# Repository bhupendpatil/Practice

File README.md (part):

<!-- prettier-ignore-start -->
# Practice

## Python
Program | Link
-- | --
Addition of Matrix | [.py](https://github.com/bhupendpatil/Practice/blob/master/Python/Addition%20of%20Matrix.py)
Bubble Sorting | [.py](https://github.com/bhupendpatil/Practice/blob/master/Python/Bubble%20Sorting.py)
Efficient Sorting | [.py](https://github.com/bhupendpatil/Practice/blob/master/Python/Efficient%20Sorting.py)
Infix to PostFix | [.py](https://github.com/bhupendpatil/Practice/blob/master/Python/Infix%20to%20PostFix.py)
Insertion Sorting | [.py](https://github.com/bhupendpatil/Practice/blob/master/Python/Insertion%20Sorting.py)
Linked List | [.py](https://github.com/bhupendpatil/Practice/blob/master/Python/Linked%20List.py)
Matching Deli | [.py](https://github.com/bhupendpatil/Practice/blob/master/Python/Matching%20Deli.py)
Palindrom Number | [.py](https://github.com/bhupendpatil/Practice/blob/master/Python/Palindrom%20Number.py)
Para Check_html | [.py](https://github.com/bhupendpatil/Practice/blob/master/Python/Para%20Check_html.py)
Para Checker | [.py](https://github.com/bhupendpatil/Practice/blob/master/Python/Para%20Checker.py)
Program based loop for odd and even numbers | [.py](https://github.com/bhupendpatil/Practice/blob/master/Python/Program%20based%20loop%20for%20odd%20and%20even%20numbers.py)
Program based on Reverse of 2 numbers | [.py](https://github.com/bhupendpatil/Practice/blob/master/Python/Program%20based%20on%20Reverse%20of%202%20numbers.py)
Program based on Reverse of 3 digit numbers | [.py](https://github.com/bhupendpatil/Practice/blob/master/Python/Program%20based%20on%20Reverse%20of%203%20digit%20numbers.py)
Program based on Reverse of 4 digit numbers using math | [.py](https://github.com/bhupendpatil/Practice/blob/master/Python/Program%20based%20on%20Reverse%20of%204%20digit%20numbers%20using%20math.py)
Program based on Swapping of two numbers | [.py](https://github.com/bhupendpatil/Practice/blob/master/Python/Program%20based%20on%20Swapping%20of%20two%20numbers.py)
Program based on loop for prime numbers | [.py](https://github.com/bhupendpatil/Practice/blob/master/Python/Program%20based%20on%20loop%20for%20prime%20numbers.py)
Program based on loops for table | [.py](https://github.com/bhupendpatil/Practice/blob/master/Python/Program%20based%20on%20loops%20for%20table.py)
Program based on to check whether the day is hot or cold | [.py](https://github.com/bhupendpatil/Practice/blob/master/Python/Program%20based%20on%20to%20check%20whether%20the%20day%20is%20hot%20or%20cold.py)
Program to check even and odd | [.py](https://github.com/bhupendpatil/Practice/blob/master/Python/Program%20to%20check%20even%20and%20odd.py)
Program to check positive or negative if it is positive then check weather it is even or odd | [.py](https://github.com/bhupendpatil/Practice/blob/master/Python/Program%20to%20check%20positive%20or%20negative%20if%20it%20is%20positive%20then%20check%20weather%20it%20is%20even%20or%20odd.py)
Program to check positive or negative or zero | [.py](https://github.com/bhupendpatil/Practice/blob/master/Python/Program%20to%20check%20positive%20or%20negative%20or%20zero.py)
Program to check whether a person is in profit or loss | [.py](https://github.com/bhupendpatil/Practice/blob/master/Python/Program%20to%20check%20whether%20a%20person%20is%20in%20profit%20or%20loss.py)
Properties | [.py](https://github.com/bhupendpatil/Practice/blob/master/Python/Properties.py)
Search Result | [.py](https://github.com/bhupendpatil/Practice/blob/master/Python/Search%20Result.py)
Simulation of Hot Potato game | [.py](https://github.com/bhupendpatil/Practice/blob/master/Python/Simulation%20of%20Hot%20Potato%20game.py)
Square Matrix | [.py](https://github.com/bhupendpatil/Practice/blob/master/Python/Square%20Matrix.py)
Stack | [.py](https://github.com/bhupendpatil/Practice/blob/master/Python/Stack.py)
String Reverse | [.py](https://github.com/bhupendpatil/Practice/blob/master/Python/String%20Reverse.py)
Absolute Sorting | [.py](https://github.com/bhupendpatil/Practice/blob/master/Python/CheckiO/Elementary/Absolute%20Sorting.py)
Binary Count | [.py](https://github.com/bhupendpatil/Practice/blob/master/Python/CheckiO/Elementary/Binary%20Count.py)
Boolean Algebra | [.py](https://github.com/bhupendpatil/Practice/blob/master/Python/CheckiO/Elementary/Boolean%20Algebra.py)
Building Base | [.py](https://github.com/bhupendpatil/Practice/blob/master/Python/CheckiO/Elementary/Building%20Base.py)
Common Words | [.py](https://github.com/bhupendpatil/Practice/blob/master/Python/CheckiO/Elementary/Common%20Words.py)
Count Inversion | [.py](https://github.com/bhupendpatil/Practice/blob/master/Python/CheckiO/Elementary/Count%20Inversion.py)
Days Between | [.py](https://github.com/bhupendpatil/Practice/blob/master/Python/CheckiO/Elementary/Days%20Between.py)
Digits Multiplication | [.py](https://github.com/bhupendpatil/Practice/blob/master/Python/CheckiO/Elementary/Digits%20Multiplication.py)
Even the last | [.py](https://github.com/bhupendpatil/Practice/blob/master/Python/CheckiO/Elementary/Even%20the%20last.py)
Fizz Buzz | [.py](https://github.com/bhupendpatil/Practice/blob/master/Python/CheckiO/Elementary/Fizz%20Buzz.py)
Friends | [.py](https://github.com/bhupendpatil/Practice/blob/master/Python/CheckiO/Elementary/Friends.py)
Index Power | [.py](https://github.com/bhupendpatil/Practice/blob/master/Python/CheckiO/Elementary/Index%20Power.py)
Monkey Typing | [.py](https://github.com/bhupendpatil/Practice/blob/master/Python/CheckiO/Elementary/Monkey%20Typing.py)
Most Numbers | [.py](https://github.com/bhupendpatil/Practice/blob/master/Python/CheckiO/Elementary/Most%20Numbers.py)
Number Base | [.py](https://github.com/bhupendpatil/Practice/blob/master/Python/CheckiO/Elementary/Number%20Base.py)
Pangram | [.py](https://github.com/bhupendpatil/Practice/blob/master/Python/CheckiO/Elementary/Pangram.py)
Right to Left | [.py](https://github.com/bhupendpatil/Practice/blob/master/Python/CheckiO/Elementary/Right%20to%20Left.py)
Secret Message | [.py](https://github.com/bhupendpatil/Practice/blob/master/Python/CheckiO/Elementary/Secret%20Message.py)
The end of other | [.py](https://github.com/bhupendpatil/Practice/blob/master/Python/CheckiO/Elementary/The%20end%20of%20other.py)
Three Words | [.py](https://github.com/bhupendpatil/Practice/blob/master/Python/CheckiO/Elementary/Three%20Words.py)
Feed Pigeons | [.py](https://github.com/bhupendpatil/Practice/blob/master/Python/CheckiO/Home/Feed%20Pigeons.py)
House Password | [.py](https://github.com/bhupendpatil/Practice/blob/master/Python/CheckiO/Home/House%20Password.py)
How to find friends | [.py](https://github.com/bhupendpatil/Practice/blob/master/Python/CheckiO/Home/How%20to%20find%20friends.py)
Median | [.py](https://github.com/bhupendpatil/Practice/blob/master/Python/CheckiO/Home/Median.py)
Moore Neighbourhood | [.py](https://github.com/bhupendpatil/Practice/blob/master/Python/CheckiO/Home/Moore%20Neighbourhood.py)
Non-unique Elements | [.py](https://github.com/bhupendpatil/Practice/blob/master/Python/CheckiO/Home/Non-unique%20Elements.py)
Pawn Brotherhood | [.py](https://github.com/bhupendpatil/Practice/blob/master/Python/CheckiO/Home/Pawn%20Brotherhood.py)
The Flat Dictionary | [.py](https://github.com/bhupendpatil/Practice/blob/master/Python/CheckiO/Home/The%20Flat%20Dictionary.py)
The Longest Palindromic | [.py](https://github.com/bhupendpatil/Practice/blob/master/Python/CheckiO/Home/The%20Longest%20Palindromic.py)
The Most Wanted Letter | [.py](https://github.com/bhupendpatil/Practice/blob/master/Python/CheckiO/Home/The%20Most%20Wanted%20Letter.py)
Xs and Os Referee | [.py](https://github.com/bhupendpatil/Practice/blob/master/Python/CheckiO/Home/Xs%20and%20Os%20Referee.py)
GCD | [.py](https://github.com/bhupendpatil/Practice/blob/master/Python/GCD.py) [.py](https://github.com/bhupendpatil/Practice/blob/master/Python/GCDLessTime.py) [.py](https://github.com/bhupendpatil/Practice/blob/master/Python/GCDmoreLessTime.py)
Insertion sort | [.py](https://github.com/bhupendpatil/Practice/blob/master/Python/1insertionSort.py) [.py](https://github.com/bhupendpatil/Practice/blob/master/Python/insertion.py)
Merge sort | [.py](https://github.com/bhupendpatil/Practice/blob/master/Python/2mergeSort.py) [.py](https://github.com/bhupendpatil/Practice/blob/master/Python/merge.py)
Permute by sorting | [.py](https://github.com/bhupendpatil/Practice/blob/master/Python/3ipermuteBySort.py)
Permute by cyclic | [.py](https://github.com/bhupendpatil/Practice/blob/master/Python/3iipermuteByCyclic.py)
Longest Common Subsequence | [.py](https://github.com/bhupendpatil/Practice/blob/master/Python/4longestCS.py) [.py](https://github.com/bhupendpatil/Practice/blob/master/Python/LCS.py)
Huffman's code | [.py](https://github.com/bhupendpatil/Practice/blob/master/Python/5huffman.py)
Kruskal's code | [.py](https://github.com/bhupendpatil/Practice/blob/master/Python/6kruskal.py)
Dijkstra's code | [.py](https://github.com/bhupendpatil/Practice/blob/master/Python/7dijkstra.py)
Euclid's code | [.py](https://github.com/bhupendpatil/Practice/blob/master/Python/8euclid.py) [ckt.py](https://github.com/bhupendpatil/Practice/blob/master/Python/euclid.py)
Euler's Theorem | [.py](https://github.com/bhupendpatil/Practice/blob/master/Python/9eulers.py)
Fermat's Theorem | [.py](https://github.com/bhupendpatil/Practice/blob/master/Python/9fermat.py)
Robot with Gear | [.py](https://github.com/bhupendpatil/Practice/blob/master/Python/Robotics/robotWithGear.py)
Robot without Gear | [.py](https://github.com/bhupendpatil/Practice/blob/master/Python/Robotics/robotWithoutGear.py)
Forward, Left, Right | [.py](https://github.com/bhupendpatil/Practice/blob/master/Python/Robotics/forwardLeftAndRight.py)
Light sensors to follow a line | [.py](https://github.com/bhupendpatil/Practice/blob/master/Python/Robotics/LightSensor.py)
Path following Robot | [.py](https://github.com/bhupendpatil/Practice/blob/master/Python/Robotics/PathFollowing.py)
Register obstacles | [.py](https://github.com/bhupendpatil/Practice/blob/master/Python/Robotics/RegisterObstacles.py)
BFS | [.py](https://github.com/bhupendpatil/Practice/blob/master/Python/BFS.py)
Do a Square (while loop) | [.py](https://github.com/bhupendpatil/Practice/blob/master/Python/Robotics/doSquareWhile.py)
Doing Steps (for loop) | [.py](https://github.com/bhupendpatil/Practice/blob/master/Python/Robotics/stepsFor.py)
Change direction based on condition | [.py](https://github.com/bhupendpatil/Practice/blob/master/Python/Robotics/directionCondition.py)
Control speed using switch case | [.py](https://github.com/bhupendpatil/Practice/blob/master/Python/Robotics/controlSpeedSwitch.py)
Simple Class | [.py](https://github.com/bhupendpatil/Practice/blob/master/Python/oopsSimp.py)
OOP init | [.py](https://github.com/bhupendpatil/Practice/blob/master/Python/oopsInit.py) [.py](https://github.com/bhupendpatil/Practice/blob/master/Python/oopsInit2.py)
OOP inheritance | [.py](https://github.com/bhupendpatil/Practice/blob/master/Python/oopsInheritance.py)
OOP overriding and overloading | [.py](https://github.com/bhupendpatil/Practice/blob/master/Python/oopsOver.py)
OOP Encapsulation | [.py](https://github.com/bhupendpatil/Practice/blob/master/Python/oopsEncapsulation.py)
OOP Private | [.py](https://github.com/bhupendpatil/Practice/blob/master/Python/oopsPrivate.py)
OOP Polymorphism | [.py](https://github.com/bhupendpatil/Practice/blob/master/Python/oopsPolymorphism.py)
Numpy Array and List | [.py](https://github.com/bhupendpatil/Practice/blob/master/Python/numpyBoot.py)
Matplotlib Boot | [.py](https://github.com/bhupendpatil/Practice/blob/master/Python/matplotlibBoot.py)
Pandas Boot | [.py](https://github.com/bhupendpatil/Practice/blob/master/Python/pandasBoot.py) [.py](https://github.com/bhupendpatil/Practice/blob/master/ML/Pandas/introduction-to-pandas.py)
Seaborn Boot | [.py](https://github.com/bhupendpatil/Practice/blob/master/Python/seabornBoot.py)

## Java
Program | Link
-- | --
AreaOfCircle | [.java](https://github.com/bhupendpatil/Practice/blob/master/Java/AreaOfCircle.java)
AreaOfRectangle | [.java](https://github.com/bhupendpatil/Practice/blob/master/Java/AreaOfRectangle.java)
AverageElement | [.java](https://github.com/bhupendpatil/Practice/blob/master/Java/AverageElement.java)
CalculateSimpleInterest | [.java](https://github.com/bhupendpatil/Practice/blob/master/Java/CalculateSimpleInterest.java)
Calculator | [.java](https://github.com/bhupendpatil/Practice/blob/master/Java/Calculator.java)
CirclePerimeter | [.java](https://github.com/bhupendpatil/Practice/blob/master/Java/CirclePerimeter.java)
ConstructorOverloadingg | [.java](https://github.com/bhupendpatil/Practice/blob/master/Java/ConstructorOverloadingg.java)
Constructorr | [.java](https://github.com/bhupendpatil/Practice/blob/master/Java/Constructorr.java)
EvenNumberList | [.java](https://github.com/bhupendpatil/Practice/blob/master/Java/EvenNumberList.java)
EvenOddNumber | [.java](https://github.com/bhupendpatil/Practice/blob/master/Java/EvenOddNumber.java)
ExceptionHandelingg | [.java](https://github.com/bhupendpatil/Practice/blob/master/Java/ExceptionHandelingg.java)
Factorial | [.java](https://github.com/bhupendpatil/Practice/blob/master/Java/Factorial.java)
FibonacciSeries | [.java](https://github.com/bhupendpatil/Practice/blob/master/Java/FibonacciSeries.java)
HelloWorld | [.java](https://github.com/bhupendpatil/Practice/blob/master/Java/HelloWorld.java)
InhertTest | [.java](https://github.com/bhupendpatil/Practice/blob/master/Java/InhertTest.java)
InterfaceTest | [.java](https://github.com/bhupendpatil/Practice/blob/master/Java/InterfaceTest.java)
JavaClasss | [.java](https://github.com/bhupendpatil/Practice/blob/master/Java/JavaClasss.java)
JavaObject | [.java](https://github.com/bhupendpatil/Practice/blob/master/Java/JavaObject.java)
MethodsOverloadingg | [.java](https://github.com/bhupendpatil/Practice/blob/master/Java/MethodsOverloadingg.java)
MultiInheritance | [.java](https://github.com/bhupendpatil/Practice/blob/master/Java/MultiInheritance.java)
MultiThreadingg | [.java](https://github.com/bhupendpatil/Practice/blob/master/Java/MultiThreadingg.java)
MultipleCatchBlock | [.java](https://github.com/bhupendpatil/Practice/blob/master/Java/MultipleCatchBlock.java)
NestingOfMethodss | [.java](https://github.com/bhupendpatil/Practice/blob/master/Java/NestingOfMethodss.java)
OddNumberList | [.java](https://github.com/bhupendpatil/Practice/blob/master/Java/OddNumberList.java)
OverRidingg | [.java](https://github.com/bhupendpatil/Practice/blob/master/Java/OverRidingg.java)
RectanglePerimeter | [.java](https://github.com/bhupendpatil/Practice/blob/master/Java/RectanglePerimeter.java)
ReversalOfAnyNumber | [.java](https://github.com/bhupendpatil/Practice/blob/master/Java/ReversalOfAnyNumber.java)
Reversalof2digits | [.java](https://github.com/bhupendpatil/Practice/blob/master/Java/Reversalof2digits.java)
Reversalof3digits | [.java](https://github.com/bhupendpatil/Practice/blob/master/Java/Reversalof3digits.java)
RunnableTest | [.java](https://github.com/bhupendpatil/Practice/blob/master/Java/RunnableTest.java)
SaralPyramid | [.java](https://github.com/bhupendpatil/Practice/blob/master/Java/SaralPyramid.java)
SingleInheritance | [.java](https://github.com/bhupendpatil/Practice/blob/master/Java/SingleInheritance.java)
SwapTwoNumbers | [.java](https://github.com/bhupendpatil/Practice/blob/master/Java/SwapTwoNumbers.java)
ThreadMethods | [.java](https://github.com/bhupendpatil/Practice/blob/master/Java/ThreadMethods.java)
ThreadPriority | [.java](https://github.com/bhupendpatil/Practice/blob/master/Java/ThreadPriority.java)
ThreadTest | [.java](https://github.com/bhupendpatil/Practice/blob/master/Java/ThreadTest.java)
TotalArea | [.java](https://github.com/bhupendpatil/Practice/blob/master/Java/TotalArea.java)
TypeCasting | [.java](https://github.com/bhupendpatil/Practice/blob/master/Java/TypeCasting.java)
UltaPyramid | [.java](https://github.com/bhupendpatil/Practice/blob/master/Java/UltaPyramid.java)
halfPyramid | [.java](https://github.com/bhupendpatil/Practice/blob/master/Java/halfPyramid.java)
Calculator | [.java](https://github.com/bhupendpatil/Practice/blob/master/Java/Calculator.java) [.java](https://github.com/bhupendpatil/Practice/blob/master/Java/Calculator_Design.java)
JComboBox | [.java](https://github.com/bhupendpatil/Practice/blob/master/Java/ComboBox.java)
Action Event | [.java](https://github.com/bhupendpatil/Practice/blob/master/Java/DemoActionEvent.java)
JButton | [.java](https://github.com/bhupendpatil/Practice/blob/master/Java/DemoButton.java)
JDBC | [.java](https://github.com/bhupendpatil/Practice/blob/master/Java/DemoDatabaseJDBC.java) [.java](https://github.com/bhupendpatil/Practice/blob/master/Java/DemoJDBC.java)
JDBC output | [.java](https://github.com/bhupendpatil/Practice/blob/master/Java/DatabaseTableOutput.java)
JDialog | [.java](https://github.com/bhupendpatil/Practice/blob/master/Java/DemoDialog.java)
JColorChooser | [.java](https://github.com/bhupendpatil/Practice/blob/master/Java/DemoJColorChooser.java) [.java](https://github.com/bhupendpatil/Practice/blob/master/Java/ColorChooser5.java)
JDesktopPane | [.java](https://github.com/bhupendpatil/Practice/blob/master/Java/DemoJDesktopPane.java) [.java](https://github.com/bhupendpatil/Practice/blob/master/Java/DesktopPane4.java)
JFileChooser | [.java](https://github.com/bhupendpatil/Practice/blob/master/Java/DemoJFileChooser.java)
JScrollPane | [.java](https://github.com/bhupendpatil/Practice/blob/master/Java/DemoJScrollPane.java) [.java](https://github.com/bhupendpatil/Practice/blob/master/Java/ScrollPane2.java)
JTabbedPane | [.java](https://github.com/bhupendpatil/Practice/blob/master/Java/DemoJTabbedPane.java) [.java](https://github.com/bhupendpatil/Practice/blob/master/Java/TabbedPane.java) [.java](https://github.com/bhupendpatil/Practice/blob/master/Java/TabbedPane3.java)
JTable | [.java](https://github.com/bhupendpatil/Practice/blob/master/Java/DemoJTable.java) [.java](https://github.com/bhupendpatil/Practice/blob/master/Java/Tablee.java) [.java](https://github.com/bhupendpatil/Practice/blob/master/Java/Table6.java)
JTextArea | [.java](https://github.com/bhupendpatil/Practice/blob/master/Java/DemoJTextArea.java)
JTextField | [.java](https://github.com/bhupendpatil/Practice/blob/master/Java/DemoJTextField.java)
JTree | [.java](https://github.com/bhupendpatil/Practice/blob/master/Java/DemoJTree.java) [.java](https://github.com/bhupendpatil/Practice/blob/master/Java/Tree7.java)
Key Event | [.java](https://github.com/bhupendpatil/Practice/blob/master/Java/DemoKeyEvent.java)
JMenu | [.java](https://github.com/bhupendpatil/Practice/blob/master/Java/DemoMenu.java)
JDBC MetaData | [.java](https://github.com/bhupendpatil/Practice/blob/master/Java/DemoMetaData.java)
Mouse Event | [.java](https://github.com/bhupendpatil/Practice/blob/master/Java/DemoMouseEvent.java)
JOptionPane | [.java](https://github.com/bhupendpatil/Practice/blob/master/Java/DemoOptionPane.java)
MultiThreading Runnable | [.java](https://github.com/bhupendpatil/Practice/blob/master/Java/DemoRunnable.java)	 
Signin Form | [.java](https://github.com/bhupendpatil/Practice/blob/master/Java/DemoSignin.java) [.java](https://github.com/bhupendpatil/Practice/blob/master/Java/LoginForm.java) [.java](https://github.com/bhupendpatil/Practice/blob/master/Java/TextAndPasswordFieldJ.java) [.java](https://github.com/bhupendpatil/Practice/blob/master/Java/Login1.java)
JSplitPane | [.java](https://github.com/bhupendpatil/Practice/blob/master/Java/DemoSplitPane.java) [.java](https://github.com/bhupendpatil/Practice/blob/master/Java/SplitPane.java)
MultiThreading Thread | [.java](https://github.com/bhupendpatil/Practice/blob/master/Java/DemoThread.java)
Window Event | [.java](https://github.com/bhupendpatil/Practice/blob/master/Java/DemoWindowEvent.java)	 
IPAddress | [.java](https://github.com/bhupendpatil/Practice/blob/master/Java/IPAddress.java)	 
IPAddress Using LH | [.java](https://github.com/bhupendpatil/Practice/blob/master/Java/IPAddressUsingLH.java)	 
InternalFrame | [.java](https://github.com/bhupendpatil/Practice/blob/master/Java/InternalFrame.java)	 
JLabel | [.java](https://github.com/bhupendpatil/Practice/blob/master/Java/LabelJ.java)
Loading | [.java](https://github.com/bhupendpatil/Practice/blob/master/Java/Loading.java)	 	 
Mixture | [.java](https://github.com/bhupendpatil/Practice/blob/master/Java/Mixture.java)
MyClient | [.java](https://github.com/bhupendpatil/Practice/blob/master/Java/MyClient.java)	 
MyServer | [.java](https://github.com/bhupendpatil/Practice/blob/master/Java/MyServer.java)	 
JPanel | [.java](https://github.com/bhupendpatil/Practice/blob/master/Java/Panel.java)	 
ServingMultipleClients | [.java](https://github.com/bhupendpatil/Practice/blob/master/Java/ServingMultipleClients.java)
SynchronizedMethod | [.java](https://github.com/bhupendpatil/Practice/blob/master/Java/SynchronizedMethod.java)
URLClass | [.java](https://github.com/bhupendpatil/Practice/blob/master/Java/URLClass.java)
JToolBar | [.java](https://github.com/bhupendpatil/Practice/blob/master/Java/demoJToolBar.java)
Radio and Check Button | [.java](https://github.com/bhupendpatil/Practice/blob/master/Java/RadioCheck11.java)
JDBC Prepared Statement | [.java](https://github.com/bhupendpatil/Practice/blob/master/Java/JDBCPrepare10.java)
JDBC insertion and display | [.java](https://github.com/bhupendpatil/Practice/blob/master/Java/JDBCIncDis9.java)
JDBC create | [.java](https://github.com/bhupendpatil/Practice/blob/master/Java/JDBCCreate8.java)
Generic Servlet | [.java](https://github.com/bhupendpatil/Practice/blob/master/Java/GenericServletDemo.java)
Current date and time using JSP | [.jsp](https://github.com/bhupendpatil/Practice/blob/master/Java/CurrentDateAndTimeJSP.jsp)
Login using Servlet | [project](https://github.com/bhupendpatil/Practice/tree/master/Java/login%20using%20servlet)
Reading Cookies | [.java](https://github.com/bhupendpatil/Practice/blob/master/Java/ReadCookie.java)
Operation of a Calculator using Servlet | [project](https://github.com/bhupendpatil/Practice/tree/master/Java/operation%20of%20a%20calculator%20using%20servlet)
addition and subtraction EJB | [project](https://github.com/bhupendpatil/Practice/tree/master/Java/addition%20and%20subtraction%20EJB)
servlet database output | [project](https://github.com/bhupendpatil/Practice/tree/master/Java/servlet%20database%20output)
Cookie Play | [project](https://github.com/bhupendpatil/Practice/tree/master/Java/Cookie%20Play)
EvenOdd Servlet | [project](https://github.com/bhupendpatil/Practice/tree/master/Java/EvenOdd%20Servlet)
PrimeServlet | [project](https://github.com/bhupendpatil/Practice/tree/master/Java/PrimeServlet)
Qualification Servlet | [project](https://github.com/bhupendpatil/Practice/tree/master/Java/Qualification%20Servlet)
Reverse String Servlet | [project](https://github.com/bhupendpatil/Practice/tree/master/Java/Reverse%20String%20Servlet)
Factorial | [project](https://github.com/bhupendpatil/Practice/tree/master/Java/Factorial)
Inserting Values to Database | [project](https://github.com/bhupendpatil/Practice/tree/master/Java/Inserting%20Values%20to%20Database)
Positive negative | [project](https://github.com/bhupendpatil/Practice/tree/master/Java/Positive%20negative)
Square Root | [project](https://github.com/bhupendpatil/Practice/tree/master/Java/Square%20Root)
Squaring Numbers | [project](https://github.com/bhupendpatil/Practice/tree/master/Java/Squaring%20Numbers)
Factorial | [.java](https://github.com/bhupendpatil/Practice/blob/master/Java/Factorial-WS.java)
Factorial1 | [.java](https://github.com/bhupendpatil/Practice/blob/master/Java/Factorial1-WS%20.java)
Palindrome | [.java](https://github.com/bhupendpatil/Practice/blob/master/Java/Palindrome-WS.java)
Power | [.java](https://github.com/bhupendpatil/Practice/blob/master/Java/Power-WS.java)
Reverse | [.java](https://github.com/bhupendpatil/Practice/blob/master/Java/Reverse-WS.java)
StringLength | [.java](https://github.com/bhupendpatil/Practice/blob/master/Java/StringLength-WS.java)
Sum | [.java](https://github.com/bhupendpatil/Practice/blob/master/Java/Sum-WS.java)
Database Login using Servlet | [project](https://github.com/bhupendpatil/Practice/tree/master/Java/DatabaseLoginServlet)
Cookie Country | [project](https://github.com/bhupendpatil/Practice/tree/master/Java/Cookie%20Country)
BFS | [.java](https://github.com/bhupendpatil/Practice/blob/master/Java/BFS.java)
Hill Climbing | [.java](https://github.com/bhupendpatil/Practice/blob/master/Java/TSPNearestNeighbour.java)
A* | [.java](https://github.com/bhupendpatil/Practice/blob/master/Java/Astar.java)
Robot with Gear | [.java](https://github.com/bhupendpatil/Practice/blob/master/Java/Robotics/robotWithGear.java)
Robot without Gear | [.java](https://github.com/bhupendpatil/Practice/blob/master/Java/Robotics/robotWithoutGear.java)
Forward, Left, Right | [.java](https://github.com/bhupendpatil/Practice/blob/master/Java/Robotics/forwardLeftAndRight.java)
Light sensors to follow a line | [.java](https://github.com/bhupendpatil/Practice/blob/master/Java/Robotics/lightSensor.java)
Path following Robot | [.java](https://github.com/bhupendpatil/Practice/blob/master/Java/Robotics/PathFollowing.java)
Register obstacles | [.java](https://github.com/bhupendpatil/Practice/blob/master/Java/Robotics/RegisterObstacles.java)
Do a Square (while loop) | [.java](https://github.com/bhupendpatil/Practice/blob/master/Java/Robotics/doSquareWhile.java)
Doing Steps (for loop) | [.java](https://github.com/bhupendpatil/Practice/blob/master/Java/Robotics/stepsFor.java)
Change direction based on condition | [.java](https://github.com/bhupendpatil/Practice/blob/master/Java/Robotics/directionCondition.java)
Control speed using switch case | [.java](https://github.com/bhupendpatil/Practice/blob/master/Java/Robotics/controlSpeedSwitch.java)
Time Server Web Service | [project](https://github.com/bhupendpatil/Practice/tree/master/Java/TimeServerWebService)
Complex DataTypes Web Service | [project](https://github.com/bhupendpatil/Practice/tree/master/Java/ComplexDataTypesWebService)
Quote for that Day | [project](https://github.com/bhupendpatil/Practice/tree/master/Java/ServerProgramQuoteDay)
Socket Message | [project](https://github.com/bhupendpatil/Practice/tree/master/Java/SocketMessage)
Multithreaded Prime Numbers | [project](https://github.com/bhupendpatil/Practice/tree/master/Java/MultithreadedPrimeNumbers)
Limit The Number Of Open Connections | [project](https://github.com/bhupendpatil/Practice/tree/master/Java/LimitTheNumberOfOpenConnections)
Pagesize Offset | [.java](https://github.com/bhupendpatil/Practice/blob/master/Java/PagesizeOffset.java)
Disk Scheduling | [.java](https://github.com/bhupendpatil/Practice/blob/master/Java/DiskScheduling.java)
Page Replacement | [project](https://github.com/bhupendpatil/Practice/tree/master/Java/PageReplacement)
Convert NFA to DFA | [.java](https://github.com/bhupendpatil/Practice/blob/master/Java/NDtoD2.java)
Convert Right Linear Grammar to Left Linear Grammar | [.java](https://github.com/bhupendpatil/Practice/blob/master/Java/R2L.java)
Generate SPM | [.java](https://github.com/bhupendpatil/Practice/blob/master/Java/SPM.java)
Generate OPM | [.java](https://github.com/bhupendpatil/Practice/blob/master/Java/opm.java)
Simple Program Analyzer And Interpreter | [project](https://github.com/bhupendpatil/Practice/tree/master/Java/SimpleProgramAnalyzerAndInterpreter)
Generate DAG | [.java](https://github.com/bhupendpatil/Practice/blob/master/Java/DAG.java)
Loop Unrolling | [.java](https://github.com/bhupendpatil/Practice/blob/master/Java/LoopUnrolling.java)
Loop Jamming | [.java](https://github.com/bhupendpatil/Practice/blob/master/Java/LoopJamming.java)
Multiplication By Strassens Algorithm | [project](https://github.com/bhupendpatil/Practice/tree/master/Java/MultiByStrassensAlgo)
CRUD operations using REST | [.txt](https://github.com/bhupendpatil/Practice/tree/master/Java/WsCrud.txt)
Human Computer Interaction Demo | [.java](https://github.com/bhupendpatil/Practice/tree/master/Java/CloseableSimpleWarning.java)
CloudSim Existing Algorithm | [.java](https://github.com/bhupendpatil/Practice/blob/master/Java/CloudSimExistingAlgo.java)
Hadoop - CharCount | [project](https://github.com/bhupendpatil/Practice/tree/master/Java/Hadoop/charcount)
Hadoop - WordCount | [project](https://github.com/bhupendpatil/Practice/tree/master/Java/Hadoop/wordcountjob)
Alon-Matias-Szegedy Algorithm | [.java](https://github.com/bhupendpatil/Practice/blob/master/Java/AMS.java)
Nth Moment | [.java](https://github.com/bhupendpatil/Practice/blob/master/Java/NthMoment.java)
Java Card Applet | [.java](https://github.com/bhupendpatil/Practice/tree/master/Java/JavaCardApplet.java)
Hadoop - WordCount | [project](https://github.com/bhupendpatil/Practice/tree/master/Java/Hadoop/matrixmulti)
Hadoop - MovieRating | [project](https://github.com/bhupendpatil/Practice/tree/master/Java/Hadoop/movierating)
Hadoop - Algebric | [project](https://github.com/bhupendpatil/Practice/tree/master/Java/Hadoop/Algebric)

## Database
Program | Link
-- | --
Create Table | [.sql](https://github.com/bhupendpatil/Practice/blob/master/Database/PL%20SQL/EMPLOYEE.sql) [.sql](https://github.com/bhupendpatil/Practice/blob/master/Database/PL%20SQL/createTable.sql)
Factorial | [.sql](https://github.com/bhupendpatil/Practice/blob/master/Database/PL%20SQL/Factorial.sql)
Associative Array | [.sql](https://github.com/bhupendpatil/Practice/blob/master/Database/PL%20SQL/associativeArray.sql)
Break | [.sql](https://github.com/bhupendpatil/Practice/blob/master/Database/PL%20SQL/break.sql)
Continue | [.sql](https://github.com/bhupendpatil/Practice/blob/master/Database/PL%20SQL/continue.sql)
Cursor | [.sql](https://github.com/bhupendpatil/Practice/blob/master/Database/PL%20SQL/cursorParameter.sql)
Case | [.sql](https://github.com/bhupendpatil/Practice/blob/master/Database/PL%20SQL/demoCase.sql)
For loop | [.sql](https://github.com/bhupendpatil/Practice/blob/master/Database/PL%20SQL/demoForLoop.sql)
Increment | [.sql](https://github.com/bhupendpatil/Practice/blob/master/Database/PL%20SQL/demoIncrement.sql)
Sequence | [.sql](https://github.com/bhupendpatil/Practice/blob/master/Database/PL%20SQL/demoSequence.sql)
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
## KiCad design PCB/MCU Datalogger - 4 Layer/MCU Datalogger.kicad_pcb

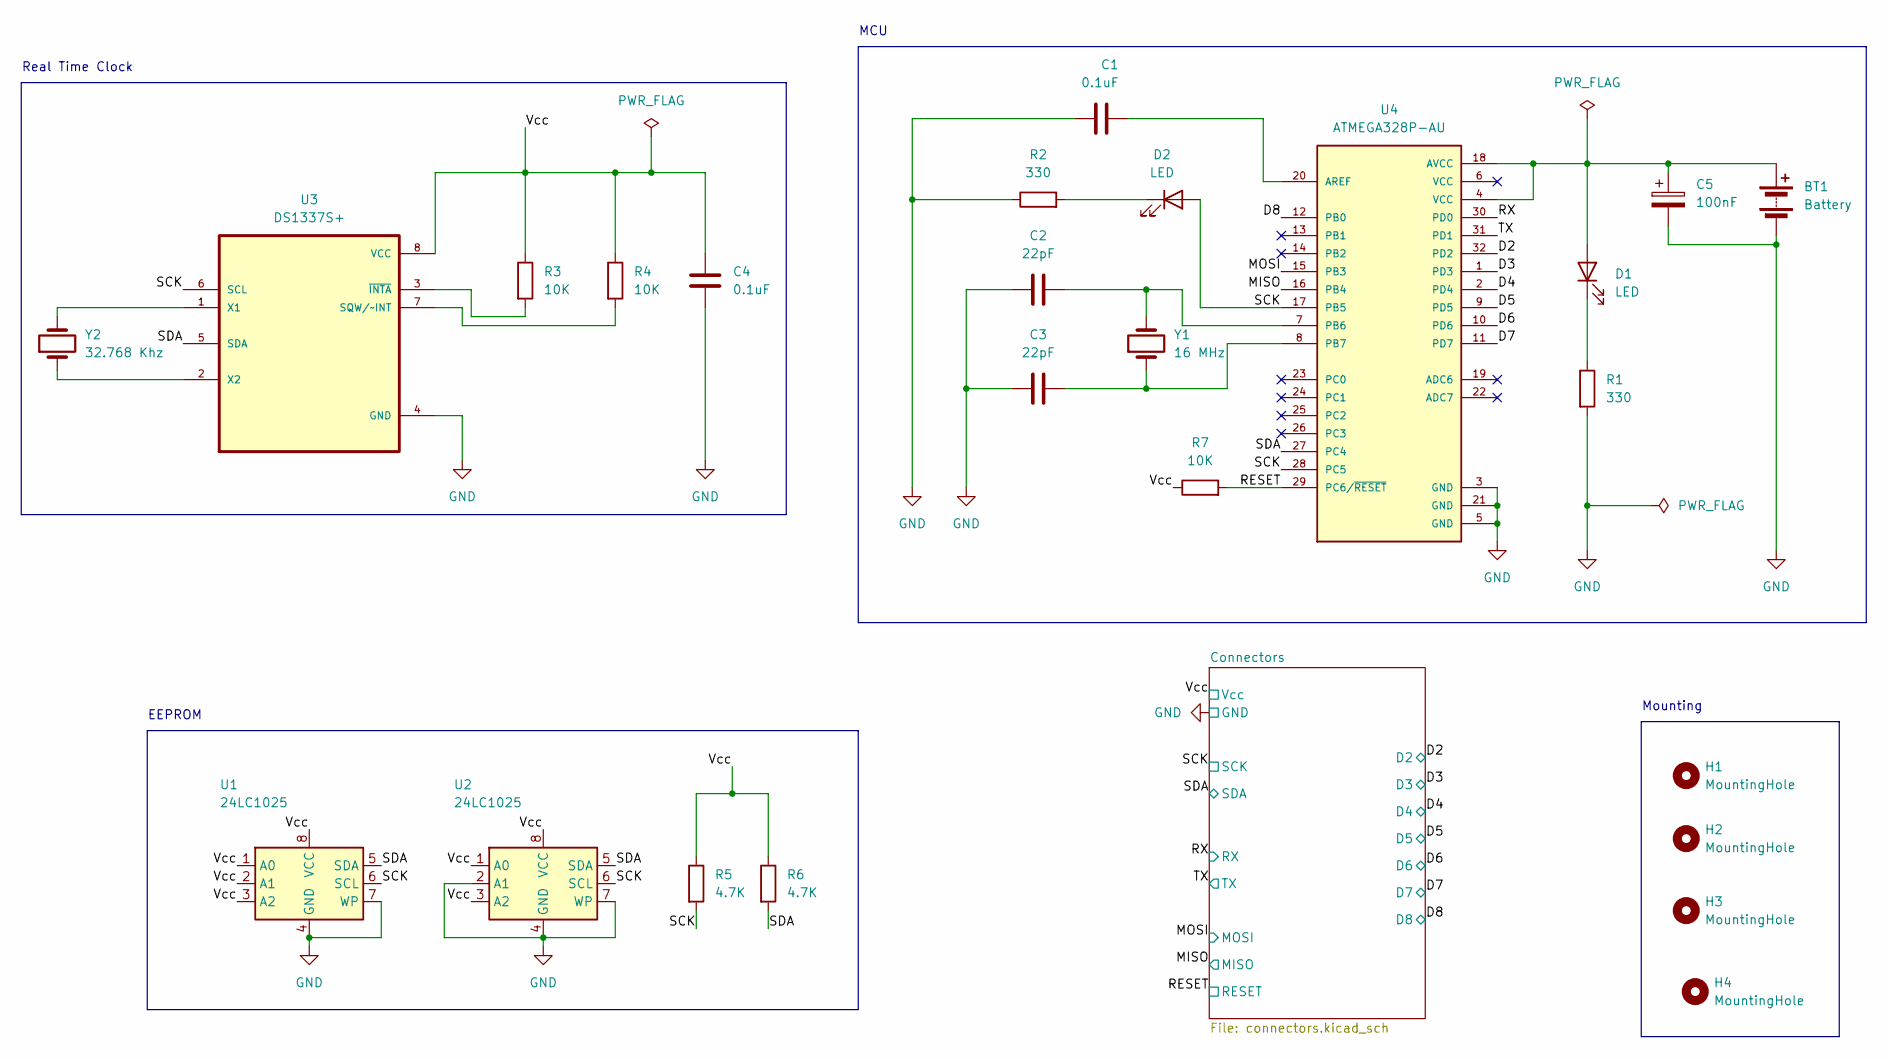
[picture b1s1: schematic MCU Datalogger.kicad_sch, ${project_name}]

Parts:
BT1: Battery; PinHeader_1x02_P2.54mm_Vertical
C1, C4: 0.1uF; C_0805_2012Metric
C2, C3: 22pF; C_0805_2012Metric
C5: 100nF; C_0805_2012Metric
D1, D2: LED; LED_0805_2012Metric
H1, H2, H3, H4: MountingHole; MountingHole_2.1mm
R1, R2: 330; R_0805_2012Metric
R3, R4, R7: 10K; R_0805_2012Metric
R5, R6: 4.7K; R_0805_2012Metric
U1, U2: 24LC1025; SOIC-8_5.23x5.23mm_P1.27mm
U3: DS1337S+; SOIC127P600X175-8N
U4: ATMEGA328P-AU; QFP80P900X900X120-32N
Y1: 16 MHz; Crystal_SMD_5032-2Pin_5.0x3.2mm_HandSoldering
Y2: 32.768 Khz; Crystal_SMD_5032-2Pin_5.0x3.2mm_HandSoldering

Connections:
/D2: U4.32 (PD2); also elsewhere on the board
/D3: U4.1 (PD3); also elsewhere on the board
/D4: U4.2 (PD4); also elsewhere on the board
/D5: U4.9 (PD5); also elsewhere on the board
/D6: U4.10 (PD6); also elsewhere on the board
/D7: U4.11 (PD7); also elsewhere on the board
/D8: U4.12 (PB0); also elsewhere on the board
/MISO: U4.16 (PB4); also elsewhere on the board
/MOSI: U4.15 (PB3); also elsewhere on the board
/RESET: R7.2, U4.29 (PC6/~RESET); also elsewhere on the board
/RX: U4.30 (PD0); also elsewhere on the board
/SCK: D2.2 (A), R5.2, U1.6 (SCL), U2.6 (SCL), U3.6 (SCL), U4.17 (PB5), U4.28 (PC5); also elsewhere on the board
/SDA: R6.2, U1.5 (SDA), U2.5 (SDA), U3.5 (SDA), U4.27 (PC4); also elsewhere on the board
/TX: U4.31 (PD1); also elsewhere on the board
GND: BT1.2 (-), C1.1, C2.1, C3.1, C4.2, C5.2, R1.2, R2.1, U1.4 (GND), U1.7 (WP), U2.2 (A1), U2.4 (GND), U2.7 (WP), U3.4 (GND), U4.3 (GND), U4.5 (GND), U4.21 (GND); also elsewhere on the board
unnamed: D1.1 (K), R1.1
unnamed: D2.1 (K), R2.2
unnamed: R4.2, U3.7 (SQW/~INT)
unnamed: U3.1 (X1), Y2.2
unnamed: U3.2 (X2), Y2.1
unnamed: R3.2, U3.3 (~INTA)
unnamed: C1.2, U4.20 (AREF)
unnamed: C2.2, U4.7 (PB6), Y1.2
unnamed: C3.2, U4.8 (PB7), Y1.1

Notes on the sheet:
EEPROM
Mounting
MCU
Real Time Clock

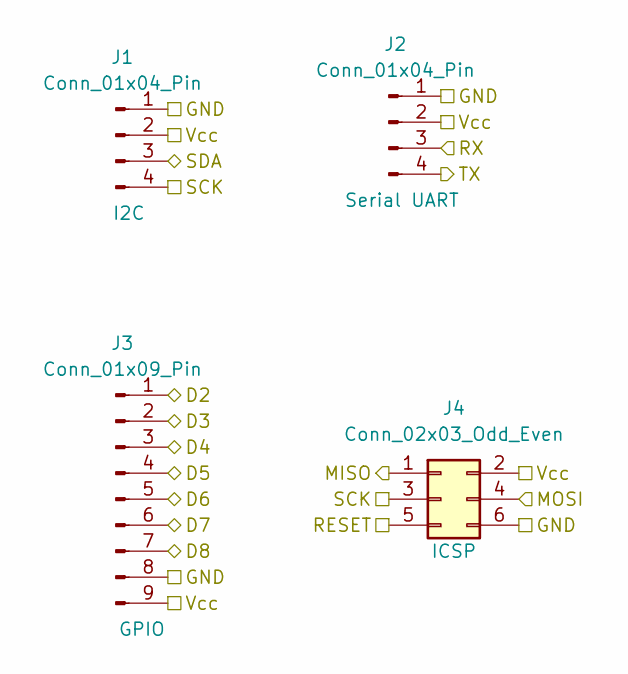
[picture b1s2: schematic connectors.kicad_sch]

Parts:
J1, J2: Conn_01x04_Pin; PinHeader_1x04_P2.54mm_Vertical
J3: Conn_01x09_Pin; PinHeader_1x09_P2.54mm_Vertical
J4: Conn_02x03_Odd_Even; PinHeader_2x03_P2.54mm_Vertical

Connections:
/D2: J3.1; also elsewhere on the board
/D3: J3.2; also elsewhere on the board
/D4: J3.3; also elsewhere on the board
/D5: J3.4; also elsewhere on the board
/D6: J3.5; also elsewhere on the board
/D7: J3.6; also elsewhere on the board
/D8: J3.7; also elsewhere on the board
/MISO: J4.1; also elsewhere on the board
/MOSI: J4.4; also elsewhere on the board
/RESET: J4.5; also elsewhere on the board
/RX: J2.3; also elsewhere on the board
/SCK: J1.4, J4.3; also elsewhere on the board
/SDA: J1.3; also elsewhere on the board
/TX: J2.4; also elsewhere on the board
GND: J1.1, J2.1, J3.8, J4.6; also elsewhere on the board

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
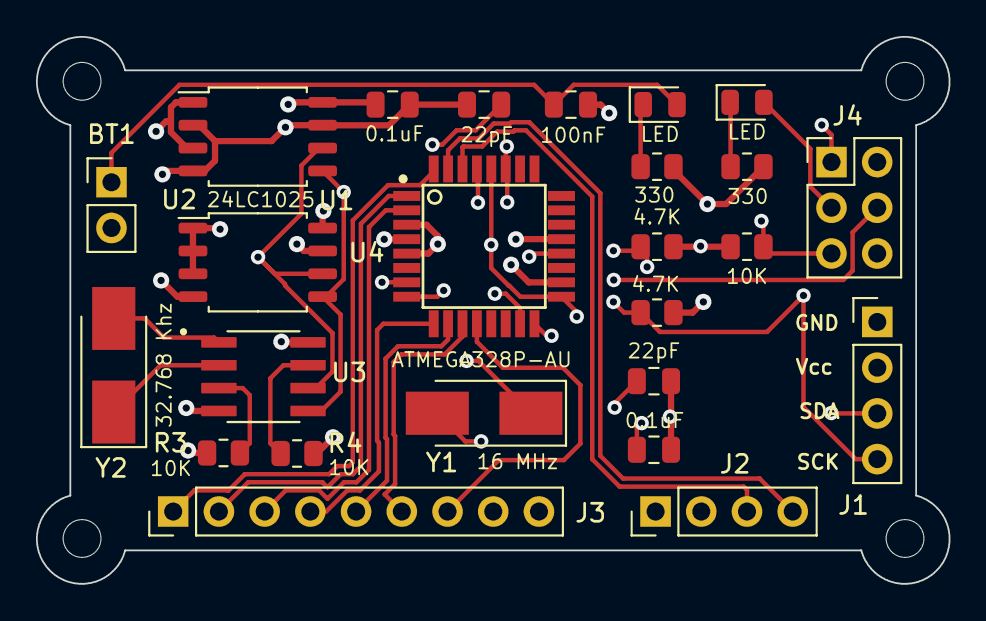
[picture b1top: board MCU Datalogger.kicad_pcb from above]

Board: 4 copper layers, 50.7 x 30.4 mm, 29 parts (0 on the bottom side), 26 nets.

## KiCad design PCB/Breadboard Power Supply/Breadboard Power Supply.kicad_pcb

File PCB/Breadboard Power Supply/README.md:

## Breadboard Power Supply

* import digikey library

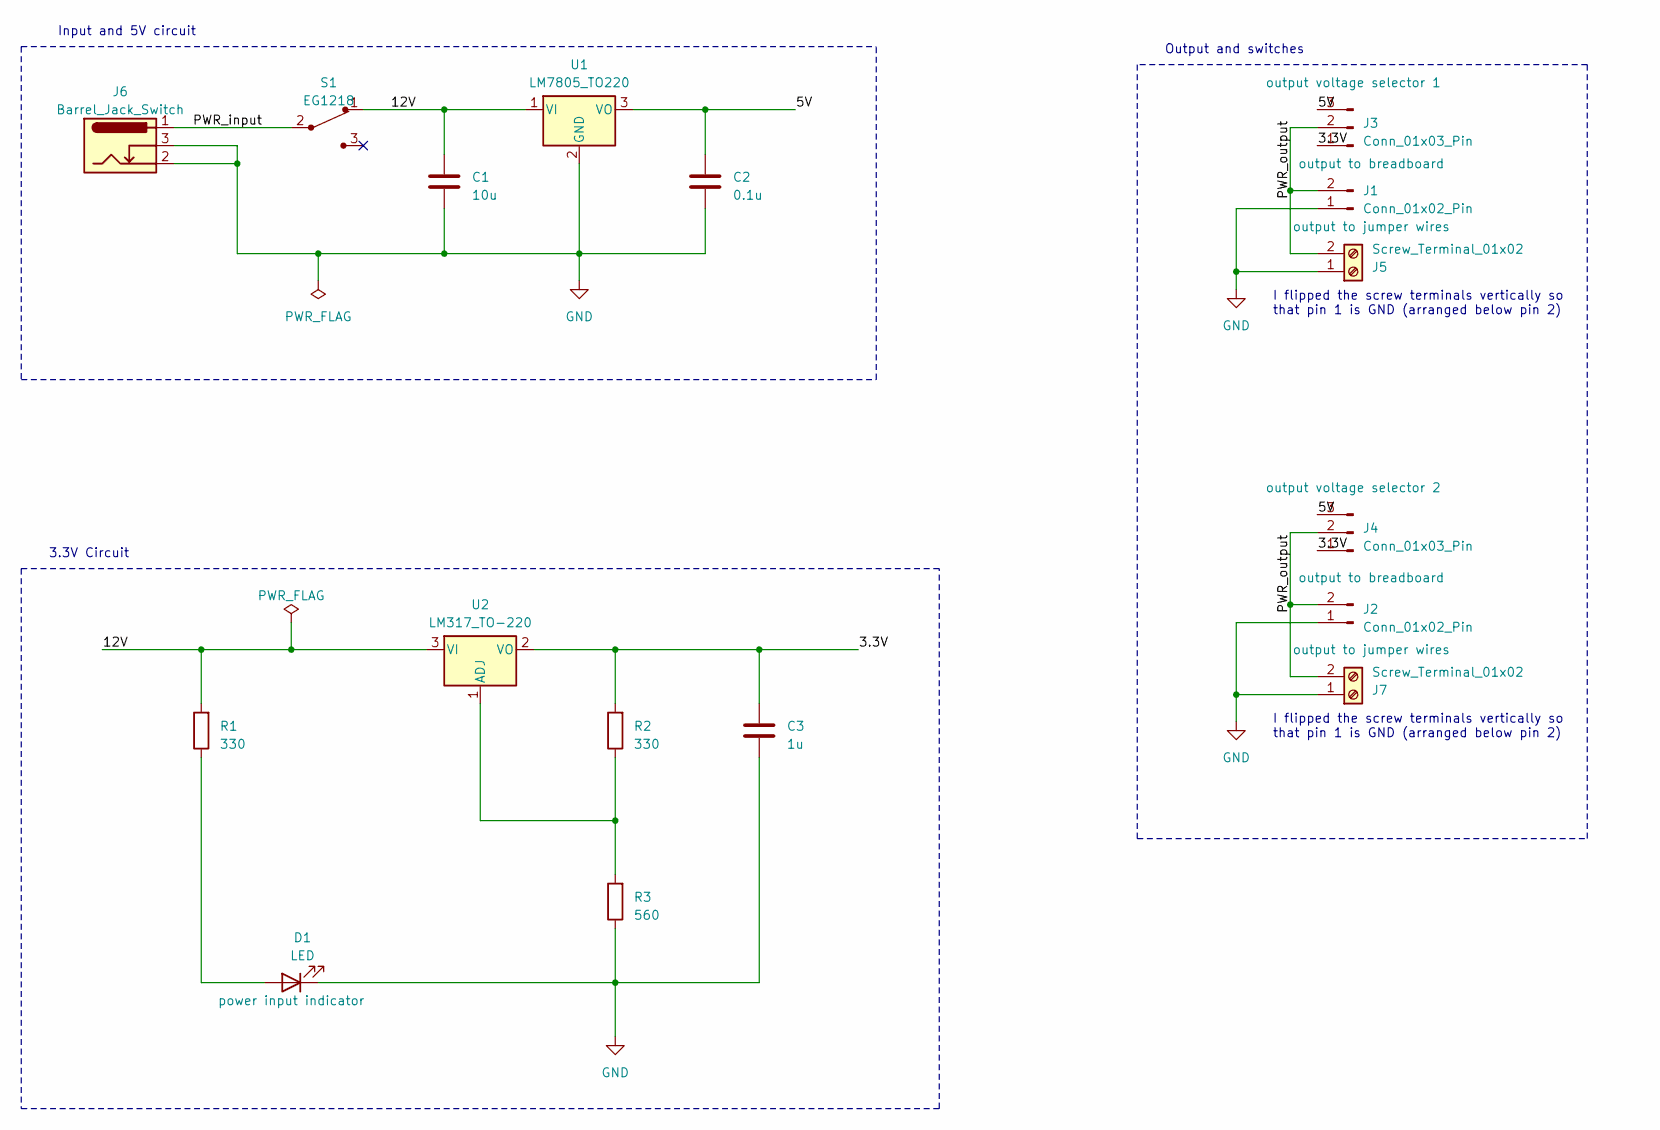
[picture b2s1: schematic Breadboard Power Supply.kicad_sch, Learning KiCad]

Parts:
C1: 10u; C_Disc_D3.0mm_W1.6mm_P2.50mm
C2: 0.1u; C_Disc_D3.0mm_W1.6mm_P2.50mm
C3: 1u; C_Disc_D3.0mm_W1.6mm_P2.50mm
D1: LED; LED_D5.0mm
J1, J2: Conn_01x02_Pin; PinHeader_1x02_P2.54mm_Vertical
J3, J4: Conn_01x03_Pin; PinHeader_1x03_P2.54mm_Vertical
J5, J7: Screw_Terminal_01x02; TerminalBlock_bornier-2_P5.08mm
J6: Barrel_Jack_Switch; BarrelJack_Horizontal
R1, R2: 330; R_Axial_DIN0204_L3.6mm_D1.6mm_P7.62mm_Horizontal
R3: 560; R_Axial_DIN0204_L3.6mm_D1.6mm_P7.62mm_Horizontal
S1: EG1218; Switch_Slide_11.6x4mm_EG1218; MPN EG1218; Digi-Key_PN EG1903-ND
U1: LM7805_TO220; TO-220-3_Vertical
U2: LM317_TO-220; TO-220-3_Vertical

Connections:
/3.3V: C3.1, J3.1, J4.1, R2.2, U2.2 (VO)
/5V: C2.1, J3.3, J4.3, U1.3 (VO)
/12V: C1.1, R1.2, S1.1, U1.1 (VI), U2.3 (VI)
/PWR_input: J6.1, S1.2
/PWR_output: J1.2, J2.2, J3.2, J4.2, J5.2, J7.2
GND: C1.2, C2.2, C3.2, D1.1 (K), J1.1, J2.1, J5.1, J6.2, J6.3, J7.1, R3.1, U1.2 (GND)
unnamed: D1.2 (A), R1.1
unnamed: R2.1, R3.2, U2.1 (ADJ)

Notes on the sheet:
Input and 5V circuit
3.3V Circuit
I flipped the screw terminals vertically so that pin 1 is GND (arranged below pin 2)
Output and switches

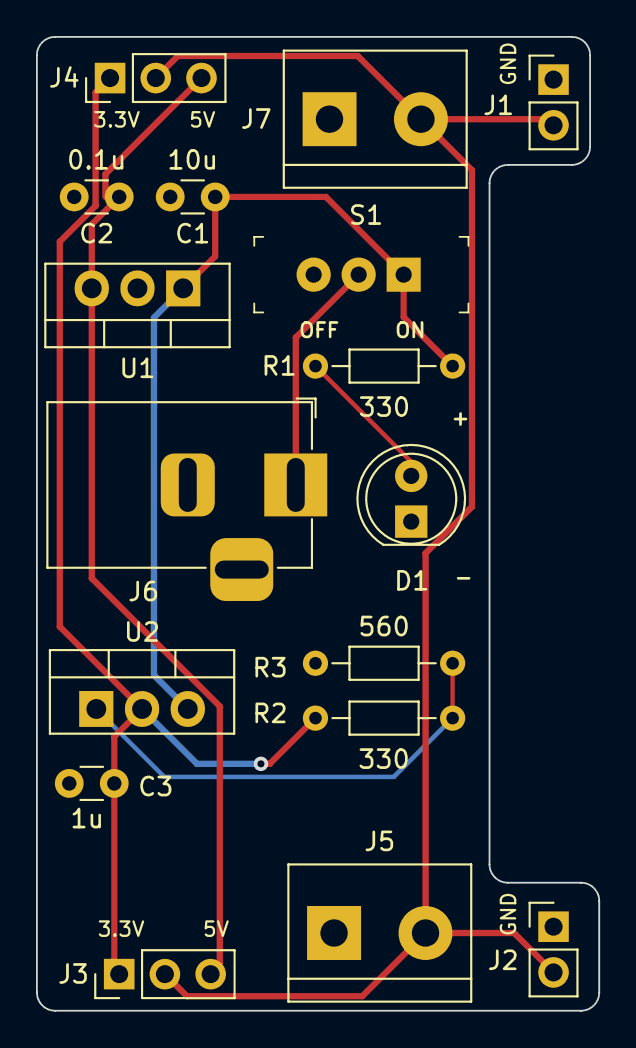
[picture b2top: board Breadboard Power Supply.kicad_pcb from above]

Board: 2 copper layers, 31.2 x 54.1 mm, 17 parts (0 on the bottom side), 8 nets.

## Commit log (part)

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2022-08-23 Bump nbconvert
    Bumps [nbconvert](https://github.com/jupyter/nbconvert) from 6.3.0 to 6.5.1.
    - [Release notes](https://github.com/jupyter/nbconvert/releases)
    - [Commits](https://github.com/jupyter/nbconvert/compare/6.3.0...6.5.1)
    ---
    updated-dependencies:
    - dependency-name: nbconvert
2022-09-23 Bump protobuf in /Deep Learning/Recurrent Networks/Generate TV Scripts
    Bumps [protobuf](https://github.com/protocolbuffers/protobuf) from 3.15.0 to 3.18.3.
    - [Release notes](https://github.com/protocolbuffers/protobuf/releases)
    - [Changelog](https://github.com/protocolbuffers/protobuf/blob/main/generate_changelog.py)
    - [Commits](https://github.com/protocolbuffers/protobuf/compare/v3.15.0...v3.18.3)
    ---
    updated-dependencies:
2022-11-21 Bump tensorflow
    Bumps [tensorflow](https://github.com/tensorflow/tensorflow) from 2.7.2 to 2.9.3.
    - [Release notes](https://github.com/tensorflow/tensorflow/releases)
    - [Changelog](https://github.com/tensorflow/tensorflow/blob/master/RELEASE.md)
    - [Commits](https://github.com/tensorflow/tensorflow/compare/v2.7.2...v2.9.3)
    ---
    updated-dependencies:
2023-02-10 Bump ipython
    Bumps [ipython](https://github.com/ipython/ipython) from 7.16.3 to 8.10.0.
    - [Release notes](https://github.com/ipython/ipython/releases)
    - [Commits](https://github.com/ipython/ipython/compare/7.16.3...8.10.0)
    ---
    updated-dependencies:
    - dependency-name: ipython
2023-03-24 Bump tensorflow-gpu
    Bumps [tensorflow-gpu](https://github.com/tensorflow/tensorflow) from 2.9.3 to 2.12.0.
    - [Release notes](https://github.com/tensorflow/tensorflow/releases)
    - [Changelog](https://github.com/tensorflow/tensorflow/blob/master/RELEASE.md)
    - [Commits](https://github.com/tensorflow/tensorflow/compare/v2.9.3...v2.12.0)
    ---
    updated-dependencies:
2023-05-22 Bump requests in /Deep Learning/Neural Networks/Sentiment Analysis
    Bumps [requests](https://github.com/psf/requests) from 2.20.0 to 2.31.0.
    - [Release notes](https://github.com/psf/requests/releases)
    - [Changelog](https://github.com/psf/requests/blob/main/HISTORY.md)
    - [Commits](https://github.com/psf/requests/compare/v2.20.0...v2.31.0)
    ---
    updated-dependencies:
2023-06-08 no pcb backups
2023-06-08 Arrange
2023-06-14 Wiring of sheet 2
2023-06-14 setup
2023-06-16 Silkscreen
2023-06-16 init
2023-07-06 Bump scipy in /Deep Learning/Recurrent Networks/Embeddings and Word2vec
    Bumps [scipy](https://github.com/scipy/scipy) from 0.19.0 to 1.10.0.
    - [Release notes](https://github.com/scipy/scipy/releases)
    - [Commits](https://github.com/scipy/scipy/compare/v0.19.0...v1.10.0)
    ---
    updated-dependencies:
    - dependency-name: scipy
2023-07-20 Bump pygments in /Deep Learning/Neural Networks/Sentiment Analysis
    Bumps [pygments](https://github.com/pygments/pygments) from 2.7.4 to 2.15.0.
    - [Release notes](https://github.com/pygments/pygments/releases)
    - [Changelog](https://github.com/pygments/pygments/blob/master/CHANGES)
    - [Commits](https://github.com/pygments/pygments/compare/2.7.4...2.15.0)
    ---
    updated-dependencies:
2023-10-25 Bump werkzeug
    Bumps [werkzeug](https://github.com/pallets/werkzeug) from 2.2.3 to 3.0.1.
    - [Release notes](https://github.com/pallets/werkzeug/releases)
    - [Changelog](https://github.com/pallets/werkzeug/blob/main/CHANGES.rst)
    - [Commits](https://github.com/pallets/werkzeug/compare/2.2.3...3.0.1)
    ---
    updated-dependencies:
2024-01-11 Bump jinja2 in /Deep Learning/Neural Networks/Sentiment Analysis
    Bumps [jinja2](https://github.com/pallets/jinja) from 2.11.3 to 3.1.3.
    - [Release notes](https://github.com/pallets/jinja/releases)
    - [Changelog](https://github.com/pallets/jinja/blob/main/CHANGES.rst)
    - [Commits](https://github.com/pallets/jinja/compare/2.11.3...3.1.3)
    ---
    updated-dependencies:
2024-05-06 Bump werkzeug
    Bumps [werkzeug](https://github.com/pallets/werkzeug) from 3.0.1 to 3.0.3.
    - [Release notes](https://github.com/pallets/werkzeug/releases)
    - [Changelog](https://github.com/pallets/werkzeug/blob/main/CHANGES.rst)
    - [Commits](https://github.com/pallets/werkzeug/compare/3.0.1...3.0.3)
    ---
    updated-dependencies:
2024-05-06 Bump jinja2 in /Deep Learning/Neural Networks/Sentiment Analysis
    Bumps [jinja2](https://github.com/pallets/jinja) from 3.1.3 to 3.1.4.
    - [Release notes](https://github.com/pallets/jinja/releases)
    - [Changelog](https://github.com/pallets/jinja/blob/main/CHANGES.rst)
    - [Commits](https://github.com/pallets/jinja/compare/3.1.3...3.1.4)
    ---
    updated-dependencies:
2024-08-02 Bump keras
    Bumps [keras](https://github.com/keras-team/keras) from 2.0.2 to 2.13.1.
    - [Release notes](https://github.com/keras-team/keras/releases)
    - [Commits](https://github.com/keras-team/keras/compare/2.0.2...v2.13.1)
    ---
    updated-dependencies:
    - dependency-name: keras
2024-10-26 Bump werkzeug
    Bumps [werkzeug](https://github.com/pallets/werkzeug) from 3.0.3 to 3.0.6.
    - [Release notes](https://github.com/pallets/werkzeug/releases)
    - [Changelog](https://github.com/pallets/werkzeug/blob/main/CHANGES.rst)
    - [Commits](https://github.com/pallets/werkzeug/compare/3.0.3...3.0.6)
    ---
    updated-dependencies:
2024-12-24 A NodeJS App
2024-12-26 commands
2025-01-08 Bump jinja2
    Bumps [jinja2](https://github.com/pallets/jinja) from 3.1.4 to 3.1.5.
    - [Release notes](https://github.com/pallets/jinja/releases)
    - [Changelog](https://github.com/pallets/jinja/blob/main/CHANGES.rst)
    - [Commits](https://github.com/pallets/jinja/compare/3.1.4...3.1.5)
    ---
    updated-dependencies:
2025-05-24 created Blockchain 💯
2025-05-24 extra storage
    overriding inherited function
2025-05-26 Library
2025-05-30 SimpleStorage
2025-06-06 forge test file
2025-06-07 refactoring the mock smart contracr
2025-06-11 Optimise the withdraw function gas costs
2025-06-11 to unit ->>
2025-06-12 .env
2025-06-13 anvil fundme simulation
2025-06-13 getBalance()
2025-06-14 added vite
2025-06-16 cleanup
2025-06-21 Usestate And Hooks
2025-06-24 Send A Tx
2025-06-24 E2E Synpress
2025-06-27 json
2025-08-30 Bump next from 15.2.4 to 15.4.7 in /Blockchain/tsmarketplace
    Bumps [next](https://github.com/vercel/next.js) from 15.2.4 to 15.4.7.
    - [Release notes](https://github.com/vercel/next.js/releases)
    - [Changelog](https://github.com/vercel/next.js/blob/canary/release.js)
    - [Commits](https://github.com/vercel/next.js/compare/v15.2.4...v15.4.7)
    ---
    updated-dependencies:
2025-09-26 Bump @metamask/sdk and wagmi in /Blockchain/tsmarketplace
    Bumps [@metamask/sdk](https://github.com/MetaMask/metamask-sdk/tree/HEAD/packages/sdk) to 0.33.1 and updates ancestor dependency [wagmi](https://github.com/wevm/wagmi/tree/HEAD/packages/react). These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
    Updates `@metamask/sdk` from 0.32.0 to 0.33.1
    - [Release notes](https://github.com/MetaMask/metamask-sdk/releases)
    - [Changelog](https://github.com/MetaMask/metamask-sdk/blob/main/packages/sdk/CHANGELOG.md)
    - [Commits](https://github.com/MetaMask/metamask-sdk/commits/@metamask/sdk@0.33.1/packages/sdk)
    Updates `wagmi` from 2.15.6 to 2.17.5
2025-12-02 Bump werkzeug
    Bumps [werkzeug](https://github.com/pallets/werkzeug) from 3.0.6 to 3.1.4.
    - [Release notes](https://github.com/pallets/werkzeug/releases)
    - [Changelog](https://github.com/pallets/werkzeug/blob/main/CHANGES.rst)
    - [Commits](https://github.com/pallets/werkzeug/compare/3.0.6...3.1.4)
    ---
    updated-dependencies:
2025-12-12 Bump next from 15.4.8 to 15.4.9 in /Blockchain/tsenderui
    Bumps [next](https://github.com/vercel/next.js) from 15.4.8 to 15.4.9.
    - [Release notes](https://github.com/vercel/next.js/releases)
    - [Changelog](https://github.com/vercel/next.js/blob/canary/release.js)
    - [Commits](https://github.com/vercel/next.js/compare/v15.4.8...v15.4.9)
    ---
    updated-dependencies:
2026-01-09 Bump werkzeug
    Bumps [werkzeug](https://github.com/pallets/werkzeug) from 3.1.4 to 3.1.5.
    - [Release notes](https://github.com/pallets/werkzeug/releases)
    - [Changelog](https://github.com/pallets/werkzeug/blob/main/CHANGES.rst)
    - [Commits](https://github.com/pallets/werkzeug/compare/3.1.4...3.1.5)
    ---
    updated-dependencies:
2026-01-21 Bump tar from 7.4.3 to 7.5.6 in /Blockchain/tsenderui
    Bumps [tar](https://github.com/isaacs/node-tar) from 7.4.3 to 7.5.6.
    - [Release notes](https://github.com/isaacs/node-tar/releases)
    - [Changelog](https://github.com/isaacs/node-tar/blob/main/CHANGELOG.md)
    - [Commits](https://github.com/isaacs/node-tar/compare/v7.4.3...v7.5.6)
    ---
    updated-dependencies:
2026-01-28 Bump next from 15.4.10 to 16.1.5 in /Blockchain/tsenderui
    Bumps [next](https://github.com/vercel/next.js) from 15.4.10 to 16.1.5.
    - [Release notes](https://github.com/vercel/next.js/releases)
    - [Changelog](https://github.com/vercel/next.js/blob/canary/release.js)
    - [Commits](https://github.com/vercel/next.js/compare/v15.4.10...v16.1.5)
    ---
    updated-dependencies:
2026-02-19 Bump tar from 7.5.7 to 7.5.9 in /Blockchain/tsenderui
    Bumps [tar](https://github.com/isaacs/node-tar) from 7.5.7 to 7.5.9.
    - [Release notes](https://github.com/isaacs/node-tar/releases)
    - [Changelog](https://github.com/isaacs/node-tar/blob/main/CHANGELOG.md)
    - [Commits](https://github.com/isaacs/node-tar/compare/v7.5.7...v7.5.9)
    ---
    updated-dependencies:
2026-02-28 Bump minimatch in /Blockchain/tsenderui
    Bumps and [minimatch](https://github.com/isaacs/minimatch). These dependencies needed to be updated together.
    Updates `minimatch` from 9.0.5 to 9.0.9
    - [Changelog](https://github.com/isaacs/minimatch/blob/main/changelog.md)
    - [Commits](https://github.com/isaacs/minimatch/compare/v9.0.5...v9.0.9)
    Updates `minimatch` from 3.1.2 to 3.1.5
    - [Changelog](https://github.com/isaacs/minimatch/blob/main/changelog.md)
2026-03-17 Bump next from 16.1.5 to 16.1.7 in /Blockchain/tsenderui
    Bumps [next](https://github.com/vercel/next.js) from 16.1.5 to 16.1.7.
    - [Release notes](https://github.com/vercel/next.js/releases)
    - [Changelog](https://github.com/vercel/next.js/blob/canary/release.js)
    - [Commits](https://github.com/vercel/next.js/compare/v16.1.5...v16.1.7)
    ---
    updated-dependencies:
2026-03-25 Bump picomatch from 4.0.2 to 4.0.4 in /Blockchain/htmlTsCoffee
    Bumps [picomatch](https://github.com/micromatch/picomatch) from 4.0.2 to 4.0.4.
    - [Release notes](https://github.com/micromatch/picomatch/releases)
    - [Changelog](https://github.com/micromatch/picomatch/blob/master/CHANGELOG.md)
    - [Commits](https://github.com/micromatch/picomatch/compare/4.0.2...4.0.4)
    ---
    updated-dependencies:
2026-04-10 Bump axios from 1.13.5 to 1.15.0 in /Blockchain/tsenderui
    Bumps [axios](https://github.com/axios/axios) from 1.13.5 to 1.15.0.
    - [Release notes](https://github.com/axios/axios/releases)
    - [Changelog](https://github.com/axios/axios/blob/v1.x/CHANGELOG.md)
    - [Commits](https://github.com/axios/axios/compare/v1.13.5...v1.15.0)
    ---
    updated-dependencies:
2026-04-22 Bump rand from 0.8.3 to 0.8.6 in /Rust/guessing_game
    Bumps [rand](https://github.com/rust-random/rand) from 0.8.3 to 0.8.6.
    - [Release notes](https://github.com/rust-random/rand/releases)
    - [Changelog](https://github.com/rust-random/rand/blob/0.8.6/CHANGELOG.md)
    - [Commits](https://github.com/rust-random/rand/compare/0.8.3...0.8.6)
    ---
    updated-dependencies:
2026-05-29 Bump axios from 1.15.2 to 1.16.0 in /Blockchain/tsenderui
    Bumps [axios](https://github.com/axios/axios) from 1.15.2 to 1.16.0.
    - [Release notes](https://github.com/axios/axios/releases)
    - [Changelog](https://github.com/axios/axios/blob/v1.x/CHANGELOG.md)
    - [Commits](https://github.com/axios/axios/compare/v1.15.2...v1.16.0)
    ---
    updated-dependencies:
